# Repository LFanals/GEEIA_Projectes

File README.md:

# GEEIA_Projectes
Des del meu punt de vista, Projectes és una assignatura que requereix una dedicació important. Els professors no faciliten l'aprenentage dels alumnes. La dificultat no rau en la matèria sinó en interpretar què és el que els professors demanen, els quals no tenen uns criteris clars. 

Aquest repositori conté els arxius de totes les entregues efectuades per l'assignatura durant el curs 2019-2020, així com la majoria dels fitxers originals necessaris per efectuar-les. L'objectiu és mostrar als futurs alumnes de l'assignatura entregues vàlides, per a què les puguin prendre com a referència. No només els documents finals els poden ajudar, sinó que fitxers com la plantilla dels documents en LaTeX o la plantilla A3 en AutoCAD els poden resultar d'utilitat.

Les entregues i fitxers no són perfectes, però juntament amb l'examen van ser suficients per assolir Matrícula d'Honor amb una mitjana de 90.4/100, que va resultar ser la millor nota d'entre els 38 estudiants que van matricular l'assignatura.

## Recomanacions

### Programes
Per fer aquesta assignatura es necessiten diversos programes que va bé tenir instal·lats el més aviat possible.
* Entorn de desenvolupament per crear i compilar documents **LaTeX** (els documents d'aquest respositori són fets així), o **Microsoft Word** en el seu defecte.   
* **AutoCAD**. Tot i existir la versió per estudiants, recomano tenir una versió completa per no tenir problemes a l'hora d'imprimir.
* **EPLAN**. És una bona eina per fer plànols elèctrics, tot i que després s'han d'exportar a AutoCAD i hi pot haver problemes de compatibilitat en alguns elements. Fer els plànols elèctrics amb AutoCAD també pot ser una bona opció.

### Generals
Em vaig emportar algunes impressions de l'assignatura que poden arribar a esdevenir consells per a futurs estudiants:
* Encara que diguin que és igual, està més ben vist imprimir els plànols en A3 que no pas en dos A4 units.
* Suposa un gran avantatge fer les entregues una setmana després d'un altre grup. Tenir algun contacte en aquest primer grup que doni feedback o que fins i tot gravi l'àudio del professor pot reduir la incertesa de què és el que el professor vol veure.
* **Aparença > Qualitat**. A les tasques d'oficina tècnica es valora més l'aparença a primer cop d'ull que no pas la qualitat de la feina feta. Fer una bona distribució d'una nau industrial és insignificant al costat de plegar correctament els plànols. Alinear bé l'índex d'un document sol tenir més importància que fer correctament uns càlculs qualssevol. Fer més volum de feina que els companys impressiona positivament.
* **Checklist > Quantitat > Qualitat**. Pel projecte tècnic, no n'hi ha prou amb l'explicat al punt anterior. A part de tenir una bona aparença en els documents és molt important fer més pàgines que la majoria, ja que molts reben la impressió que, per aquest fet, s'ha fet més feina i la dificultat és major. Encara més important que això és no tenir cap error de checklist, els quals només despuntuen. 3 errors de checklist suposen un suspens. Un treball amb moltes pàgines i sense errors de checklist és gairebé sinónim de bona nota.
* A l'entrega final del projecte tècnic són els companys els que marquen la nota de partida. Impressionar-los suposa tenir moltes garanties de ser ben qualificat pels professors.
* Amb tot això dit, sembla lògic afirmar que el millor tema que un pot escollir pel projecte tècnic no és un que domini, sinó un que li doni plànols, taules, càlculs i, en general, moltes pàgines amb la mínima dedicació possible. Intentar ajuntar disciplines diferents com programació i plaques solars com vaig fer en el meu projecte dóna l'aparença de projecte multidisciplinar i de dedicació.  
* Fer projectes tècnics diferents a la majoria de companys es valora positivament. El meu any van sorgir molts treballs de plaques solars i tots van ser catalogats de molt similars, fins al punt de que encara que estiguessin ben fets, la seva nota era inferior respecte altres treballs de menys qualitat. Fer un treball d'electrònica o programació dóna més facilitats de diferenciar-se.

## Disclaimer
Tothom és lliure de baixar-se, modificar i treballar amb el present en aquest repositori. Es recomana inspirar-se, però no copiar.

L'autor d'aquest repositori no assegura resultats als que utilitzin els seus fitxers i segueixin les seves recomanacions.

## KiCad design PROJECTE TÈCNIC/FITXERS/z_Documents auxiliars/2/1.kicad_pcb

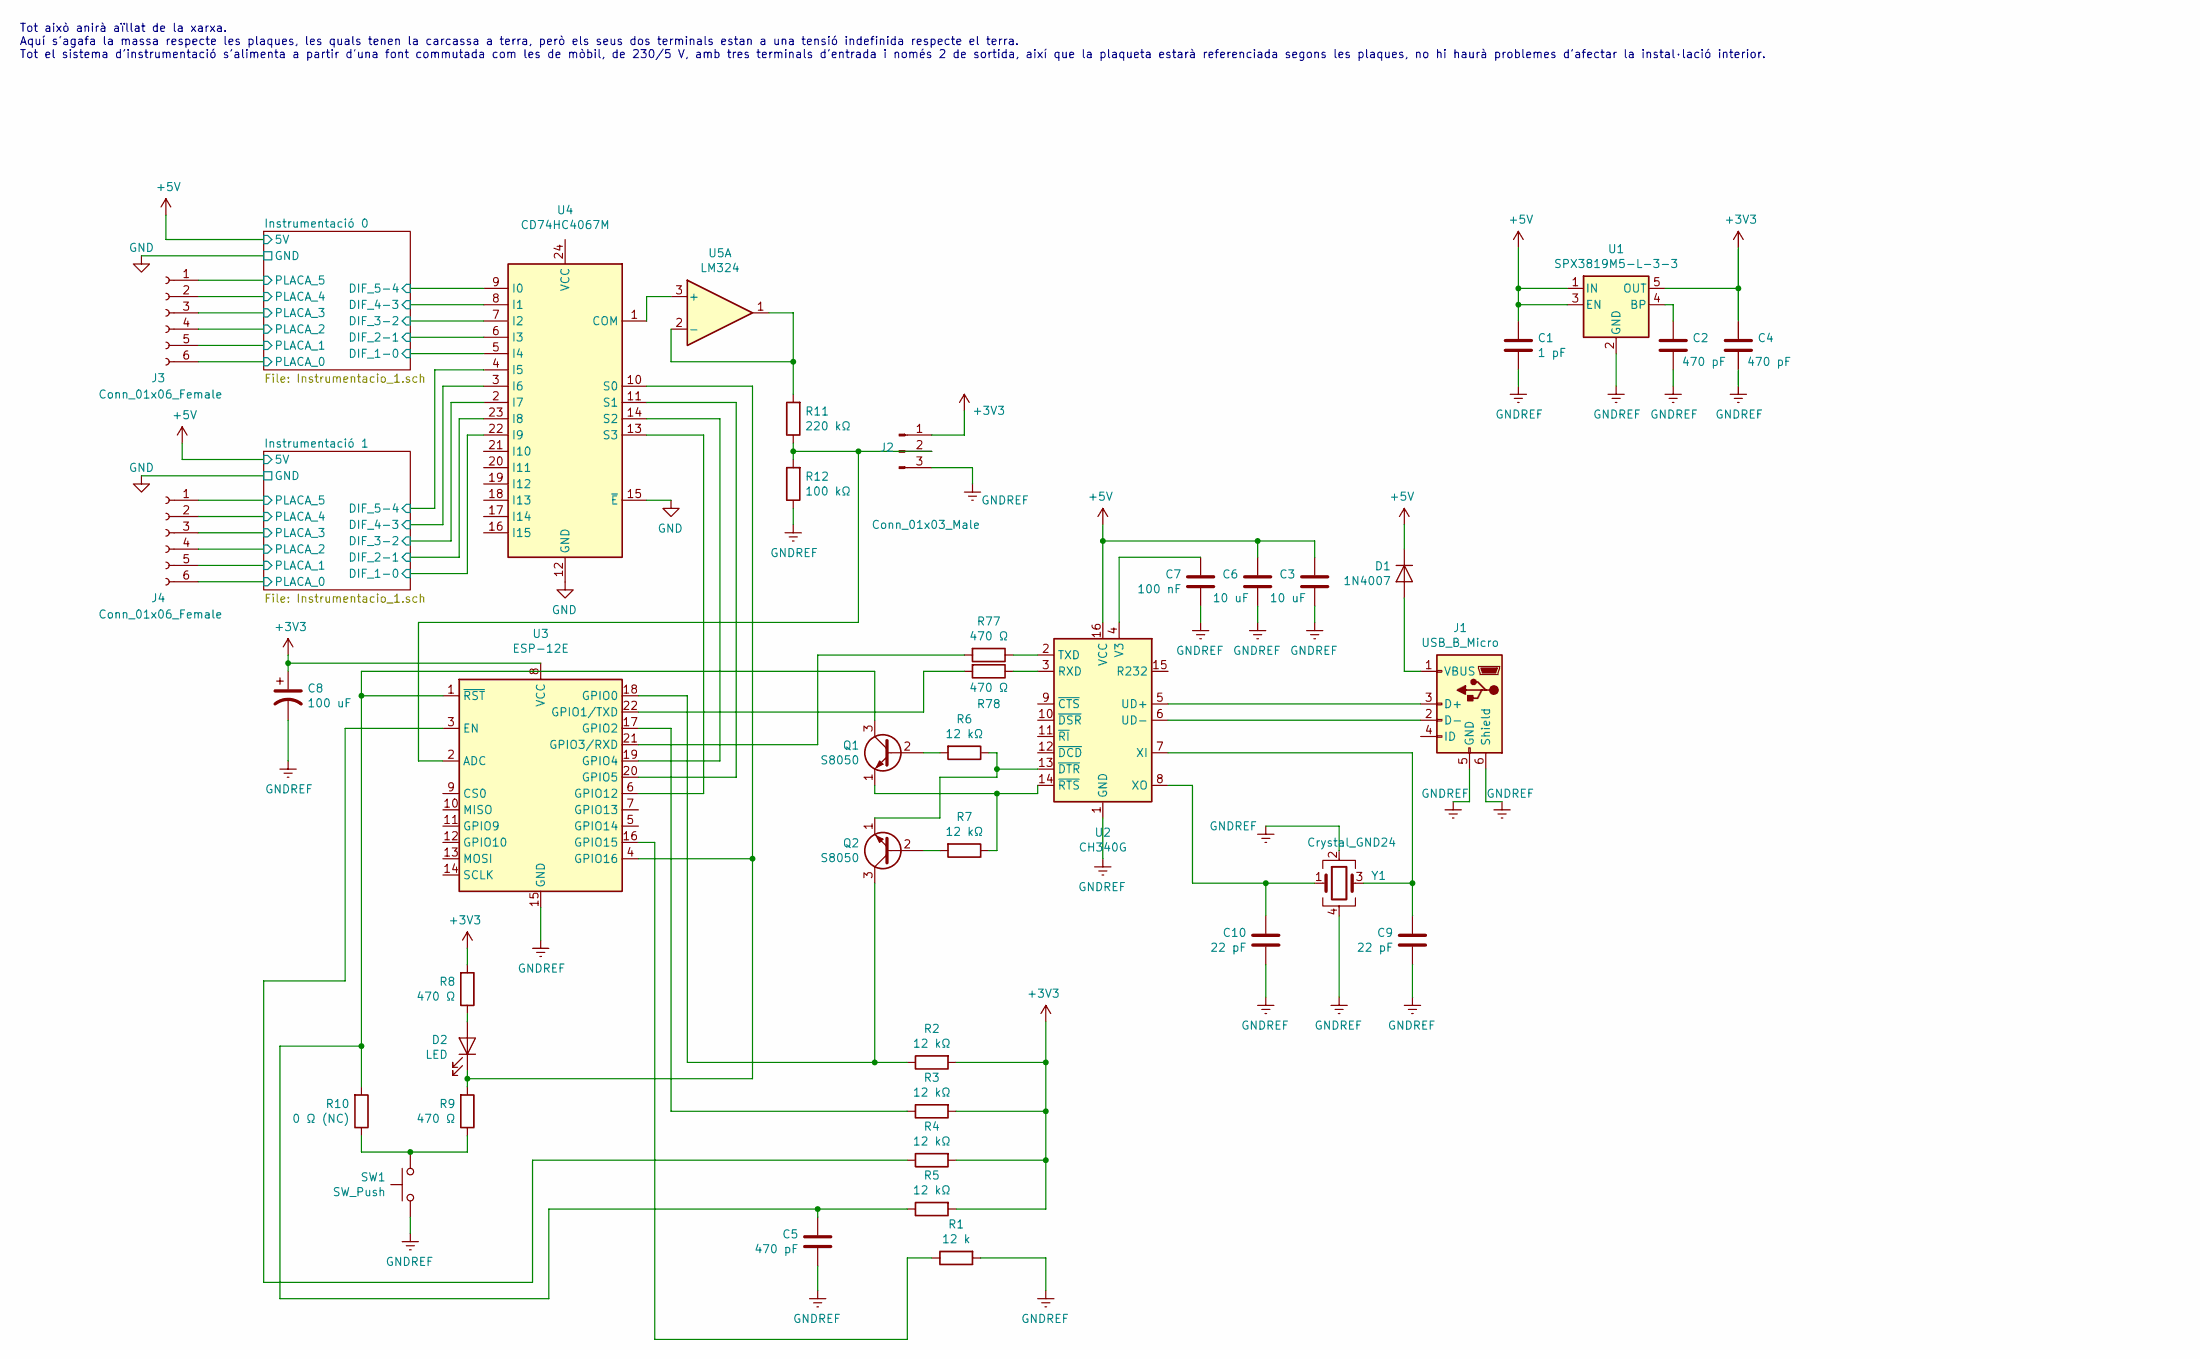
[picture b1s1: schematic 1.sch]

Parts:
C1: 1 pF; C_1206_3216Metric
C2, C4, C5: 470 pF; C_1206_3216Metric
C3, C6: 10 uF; C_1206_3216Metric
C7: 100 nF; C_1206_3216Metric
C8: 100 uF; C_Radial_D10.0mm_H20.0mm_P5.00mm
C9, C10: 22 pF; C_1206_3216Metric
D1: 1N4007; D_DO-41_SOD81_P10.16mm_Horizontal
D2: LED; LED_1206_3216Metric
J1: USB_B_Micro; USB_Micro-B_Molex-105133-0001
J2: Conn_01x03_Male; PinHeader_1x03_P2.54mm_Vertical
J3, J4: Conn_01x06_Female; TerminalBlock_bornier-6_P5.08mm
Q1, Q2: S8050; TO-92_Inline
R1: 12 k; R_1206_3216Metric
R2, R3, R4, R5, R6, R7: 12 kΩ; R_1206_3216Metric
R8, R9, R77, R78: 470 Ω; R_1206_3216Metric
R10: 0 Ω (NC); R_1206_3216Metric
R11: 220 kΩ; R_1206_3216Metric
R12: 100 kΩ; R_1206_3216Metric
SW1: SW_Push; R_1206_3216Metric
U1: SPX3819M5-L-3-3; SOT-23-5
U2: CH340G; SOIC-16_3.9x9.9mm_P1.27mm
U3: ESP-12E
U4: CD74HC4067M; SOIC-24W_7.5x15.4mm_P1.27mm
U5: LM324; SOIC-14_3.9x8.7mm_P1.27mm
Y1: Crystal_GND24; Oscillator_SMD_TXC_7C-4Pin_5.0x3.2mm

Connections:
+3V3: C4.1, C8.1, J2.1, R2.2, R3.2, R4.2, R5.2, R8.2, U1.5 (OUT), U3.8 (VCC)
+5V: C1.1, C3.1, C6.1, D1.1 (K), U1.1 (IN), U1.3 (EN), U2.16 (VCC); also elsewhere on the board
/Instrumentació 0/DIF_1-0: U4.5 (I4); also elsewhere on the board
/Instrumentació 0/DIF_2-1: U4.6 (I3); also elsewhere on the board
/Instrumentació 0/DIF_3-2: U4.7 (I2); also elsewhere on the board
/Instrumentació 0/DIF_4-3: U4.8 (I1); also elsewhere on the board
/Instrumentació 0/DIF_5-4: U4.9 (I0); also elsewhere on the board
/Instrumentació 0/PLACA_0: J3.6; also elsewhere on the board
/Instrumentació 0/PLACA_1: J3.5; also elsewhere on the board
/Instrumentació 0/PLACA_2: J3.4; also elsewhere on the board
/Instrumentació 0/PLACA_3: J3.3; also elsewhere on the board
/Instrumentació 0/PLACA_4: J3.2; also elsewhere on the board
/Instrumentació 0/PLACA_5: J3.1; also elsewhere on the board
/Instrumentació 1/DIF_1-0: U4.22 (I9); also elsewhere on the board
/Instrumentació 1/DIF_2-1: U4.23 (I8); also elsewhere on the board
/Instrumentació 1/DIF_5-4: U4.4 (I5); also elsewhere on the board
/Instrumentació 1/PLACA_0: J4.6; also elsewhere on the board
/Instrumentació 1/PLACA_1: J4.5; also elsewhere on the board
/Instrumentació 1/PLACA_2: J4.4; also elsewhere on the board
/Instrumentació 1/PLACA_3: J4.3; also elsewhere on the board
/Instrumentació 1/PLACA_4: J4.2; also elsewhere on the board
/Instrumentació 1/PLACA_5: J4.1; also elsewhere on the board
GND: U4.12 (GND), U4.15 (~E); also elsewhere on the board
GNDREF: C1.2, C2.2, C3.2, C4.2, C5.2, C6.2, C7.2, C8.2, C9.2, C10.2, J1.5 (GND), J1.6 (Shield), J2.3, R1.2, R12.1, SW1.2, U1.2 (GND), U2.1 (GND), U3.15 (GND), Y1.2, Y1.4; also elsewhere on the board
unnamed: C2.1, U1.4 (BP)
unnamed: C5.1, Q1.3 (C), R5.1, R10.2, U3.1 (~RST)
unnamed: C7.1, U2.4 (V3)
unnamed: C9.1, U2.7 (XI), Y1.3
unnamed: C10.1, U2.8 (XO), Y1.1
unnamed: D1.2 (A), J1.1 (VBUS)
unnamed: D2.1 (K), R9.2, U3.4 (GPIO16), U4.10 (S0)
unnamed: D2.2 (A), R8.1
unnamed: J1.2 (D-), U2.6 (UD-)
unnamed: J1.3 (D+), U2.5 (UD+)
unnamed: J2.2, R11.1, R12.2, U3.2 (ADC)
unnamed: Q1.1 (E), R7.1, U2.14 (~RTS)
unnamed: Q1.2 (B), R6.2
unnamed: Q2.1 (E), R6.1, U2.13 (~DTR)
unnamed: Q2.2 (B), R7.2
unnamed: Q2.3 (C), R2.1, U3.18 (GPIO0)
unnamed: R1.1, U3.16 (GPIO15)
unnamed: R3.1, U3.17 (GPIO2)
unnamed: R4.1, U3.3 (EN)
unnamed: R9.1, R10.1, SW1.1
unnamed: R11.2, U5.1, U5.2 (-)
unnamed: R77.1, U2.2 (TXD)
unnamed: R77.2, U3.21 (GPIO3/RXD)
unnamed: R78.1, U2.3 (RXD)
unnamed: R78.2, U3.22 (GPIO1/TXD)
unnamed: U3.6 (GPIO12), U4.13 (S3)
unnamed: U3.19 (GPIO4), U4.14 (S2)
unnamed: U3.20 (GPIO5), U4.11 (S1)
unnamed: U4.1 (COM), U5.3 (+)

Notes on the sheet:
Tot això anirà aïllat de la xarxa. Aquí s'agafa la massa respecte les plaques, les quals tenen la carcassa a terra, però els seus dos terminals estan a una tensió indefinida respecte el terra. Tot el sistema d'instrumentació s'alimenta a partir d'una font commutada com les de mòbil, de 230/5 V, amb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

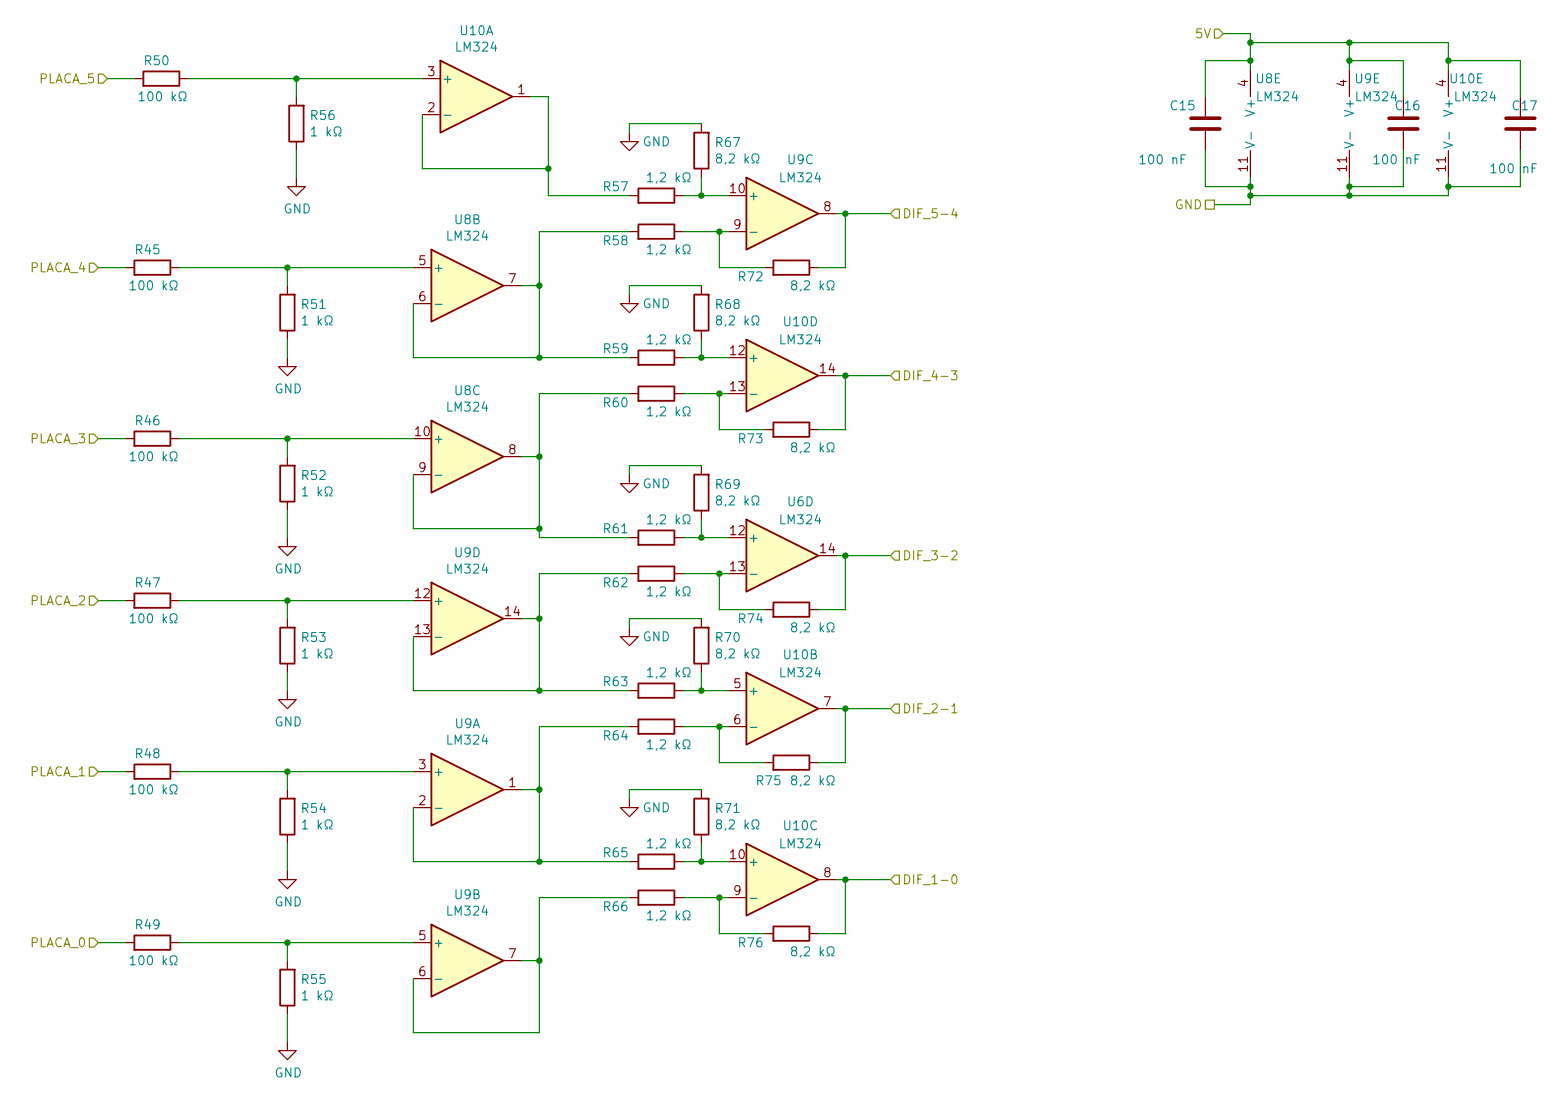
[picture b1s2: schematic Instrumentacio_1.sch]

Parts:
C12, C13, C14: 100 nF; C_1206_3216Metric
R13, R14, R15, R16, R17, R18: 100 kΩ; R_1206_3216Metric
R19, R20, R21, R22, R23, R24: 1 kΩ; R_1206_3216Metric
R25, R26, R27, R28, R29, R30, R31, R32, R33, R34: 1,2 kΩ; R_1206_3216Metric
R35, R36, R37, R38, R39, R40, R41, R42, R43, R44: 8,2 kΩ; R_1206_3216Metric
U5, U6, U7, U8: LM324; SOIC-14_3.9x8.7mm_P1.27mm

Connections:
+5V: C12.1, C13.1, C14.1, U5.4 (V+), U6.4 (V+), U7.4 (V+), U8.4 (V+); also elsewhere on the board
/Instrumentació 1/DIF_1-0: R44.1, U7.8; also elsewhere on the board
/Instrumentació 1/DIF_2-1: R43.1, U7.7; also elsewhere on the board
/Instrumentació 1/DIF_5-4: R40.1, U6.8; also elsewhere on the board
/Instrumentació 1/PLACA_0: R17.2; also elsewhere on the board
/Instrumentació 1/PLACA_1: R16.2; also elsewhere on the board
/Instrumentació 1/PLACA_2: R15.2; also elsewhere on the board
/Instrumentació 1/PLACA_3: R14.2; also elsewhere on the board
/Instrumentació 1/PLACA_4: R13.2; also elsewhere on the board
/Instrumentació 1/PLACA_5: R18.2; also elsewhere on the board
GND: C12.2, C13.2, C14.2, R19.1, R20.1, R21.1, R22.1, R23.1, R24.1, R35.2, R36.2, R37.2, R38.2, R39.2, U5.11 (V-), U6.11 (V-), U7.11 (V-), U8.11 (V-); also elsewhere on the board
unnamed: R13.1, R19.2, U5.5 (+)
unnamed: R14.1, R20.2, U5.10 (+)
unnamed: R15.1, R21.2, U7.12 (+)
unnamed 51: R16.1, R22.2, U6.3 (+); also elsewhere on the board
unnamed 52: R17.1, R23.2, U6.5 (+); also elsewhere on the board
unnamed: R18.1, R24.2, U7.3 (+)
unnamed 54: R25.1, R35.1, U6.10 (+); also elsewhere on the board
unnamed: R25.2, U7.1, U7.2 (-)
unnamed 56: R26.1, R40.2, U6.9 (-); also elsewhere on the board
unnamed: R26.2, R27.2, U5.6 (-), U5.7
unnamed: R28.2, R29.2, U5.8, U5.9 (-)
unnamed: R30.2, R31.2, U7.13 (-), U7.14
unnamed: R31.1, R38.1, U7.5 (+)
unnamed: R32.1, R43.2, U7.6 (-)
unnamed 62: R32.2, R33.2, U6.1, U6.2 (-); also elsewhere on the board
unnamed: R33.1, R39.1, U7.10 (+)
unnamed: R34.1, R44.2, U7.9 (-)
unnamed 65: R34.2, U6.6 (-), U6.7; also elsewhere on the board
unnamed 66: U8.5 (+); also elsewhere on the board
unnamed 67: U8.10 (+); also elsewhere on the board
unnamed 75: U8.6 (-), U8.7; also elsewhere on the board
unnamed 78: U8.8, U8.9 (-); also elsewhere on the board

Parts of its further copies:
C15, C16, C17: 100 nF; C_1206_3216Metric
R45, R46, R47, R48, R49, R50: 100 kΩ; R_1206_3216Metric
R51, R52, R53, R54, R55, R56: 1 kΩ; R_1206_3216Metric
R57, R58, R59, R60, R61, R62, R63, R64, R65, R66: 1,2 kΩ; R_1206_3216Metric
R67, R68, R69, R70, R71, R72, R73, R74, R75, R76: 8,2 kΩ; R_1206_3216Metric
U9, U10: LM324; SOIC-14_3.9x8.7mm_P1.27mm

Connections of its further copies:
+5V: C15.1, C16.1, C17.1, U9.4 (V+), U10.4 (V+); also elsewhere on the board
/Instrumentació 0/DIF_1-0: R76.1, U10.8; also elsewhere on the board
/Instrumentació 0/DIF_2-1: R75.1, U10.7; also elsewhere on the board
/Instrumentació 0/DIF_3-2: R74.1; also elsewhere on the board
/Instrumentació 0/DIF_4-3: R73.1, U10.14; also elsewhere on the board
/Instrumentació 0/DIF_5-4: R72.1, U9.8; also elsewhere on the board
/Instrumentació 0/PLACA_0: R49.2; also elsewhere on the board
/Instrumentació 0/PLACA_1: R48.2; also elsewhere on the board
/Instrumentació 0/PLACA_2: R47.2; also elsewhere on the board
/Instrumentació 0/PLACA_3: R46.2; also elsewhere on the board
/Instrumentació 0/PLACA_4: R45.2; also elsewhere on the board
/Instrumentació 0/PLACA_5: R50.2; also elsewhere on the board
GND: C15.2, C16.2, C17.2, R51.1, R52.1, R53.1, R54.1, R55.1, R56.1, R67.2, R68.2, R69.2, R70.2, R71.2, U9.11 (V-), U10.11 (V-); also elsewhere on the board
unnamed 66: R45.1, R51.2; also elsewhere on the board
unnamed 67: R46.1, R52.2; also elsewhere on the board
unnamed: R47.1, R53.2, U9.12 (+)
unnamed: R48.1, R54.2, U9.3 (+)
unnamed: R49.1, R55.2, U9.5 (+)
unnamed: R50.1, R56.2, U10.3 (+)
unnamed: R57.1, R67.1, U9.10 (+)
unnamed: R57.2, U10.1, U10.2 (-)
unnamed: R58.1, R72.2, U9.9 (-)
unnamed 75: R58.2, R59.2; also elsewhere on the board
unnamed: R59.1, R68.1, U10.12 (+)
unnamed: R60.1, R73.2, U10.13 (-)
unnamed 78: R60.2, R61.2; also elsewhere on the board
unnamed 79: R61.1, R69.1; also elsewhere on the board
unnamed 80: R62.1, R74.2; also elsewhere on the board
unnamed: R62.2, R63.2, U9.13 (-), U9.14
unnamed: R63.1, R70.1, U10.5 (+)
unnamed: R64.1, R75.2, U10.6 (-)
unnamed: R64.2, R65.2, U9.1, U9.2 (-)
unnamed: R65.1, R71.1, U10.10 (+)
unnamed: R66.1, R76.2, U10.9 (-)
unnamed: R66.2, U9.6 (-), U9.7

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
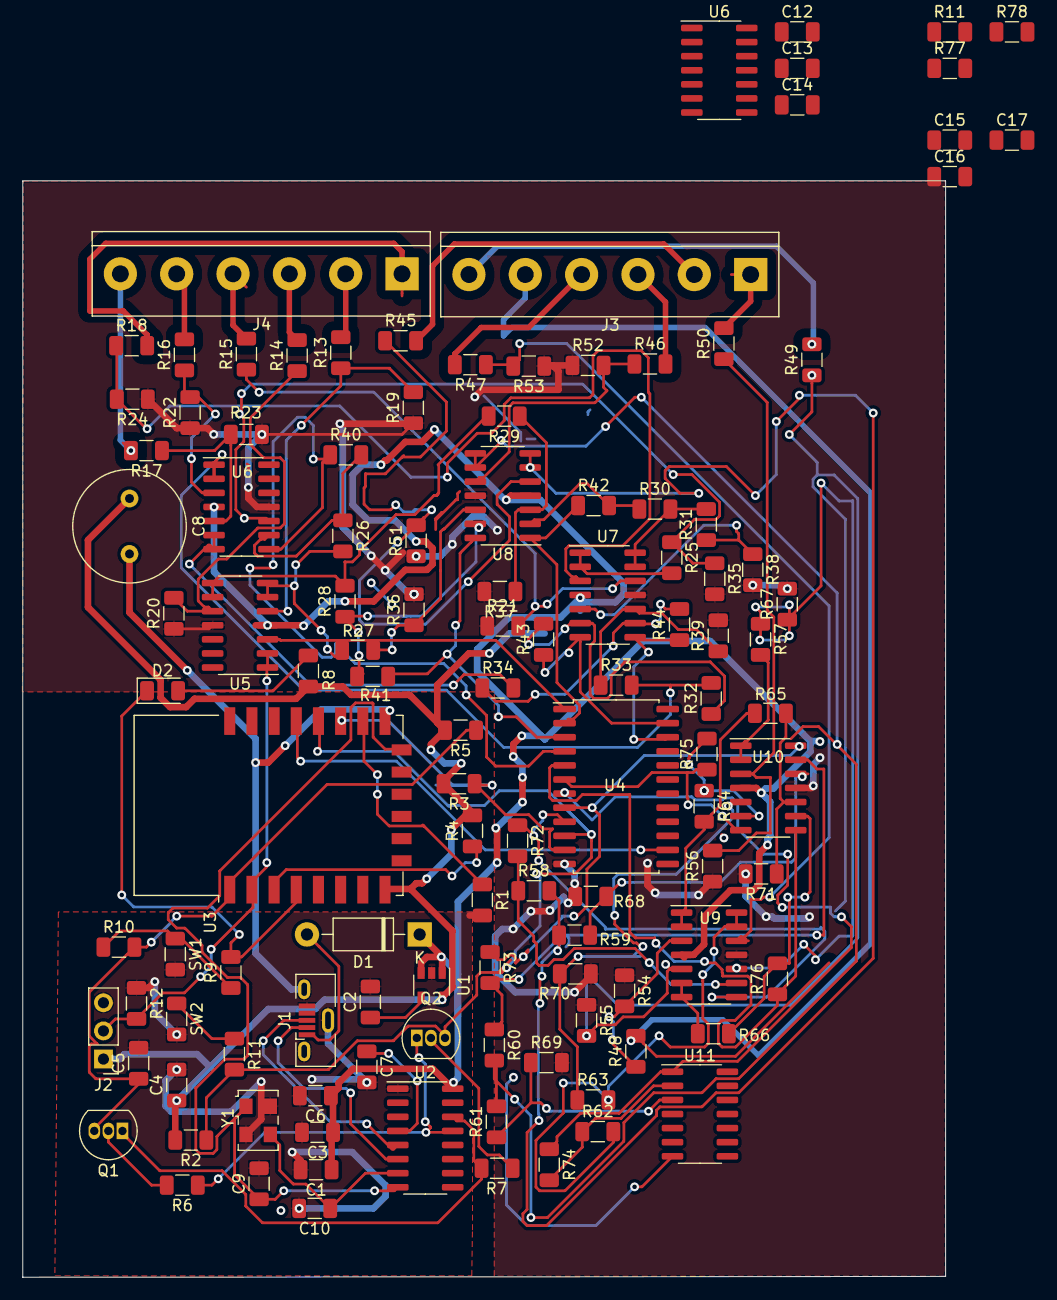
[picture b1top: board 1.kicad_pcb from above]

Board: 2 copper layers, 83.2 x 98.9 mm, 118 parts (0 on the bottom side), 100 nets.

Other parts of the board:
R11#2: 470 Ω; R_1206_3216Metric
SW2: SW_Push; R_1206_3216Metric
U6#2, U11: LM324; SOIC-14_3.9x8.7mm_P1.27mm

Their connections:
+5V: U6#2.4; also elsewhere on the board
/Instrumentació 0/DIF_3-2: U11.1; also elsewhere on the board
/Instrumentació 1/DIF_5-4: U6#2.8; also elsewhere on the board
GND: U6#2.11; also elsewhere on the board
GNDREF: SW2.2; also elsewhere on the board
unnamed: R11#2.1, SW2.1
unnamed 51: U6#2.3; also elsewhere on the board
unnamed 52: U6#2.5; also elsewhere on the board
unnamed 54: U6#2.10; also elsewhere on the board
unnamed 56: U6#2.9; also elsewhere on the board
unnamed 62: U6#2.1, U6#2.2; also elsewhere on the board
unnamed 65: U6#2.6, U6#2.7; also elsewhere on the board
unnamed 79: U11.3; also elsewhere on the board
unnamed 80: U11.2; also elsewhere on the board

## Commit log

2020-09-11 README update
2020-09-11 Last commit
